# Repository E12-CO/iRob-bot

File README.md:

# iRob-bot

iRob-bot is a robot testing platform for Arduino and ROS2.
The goal is to have a autonomous robot with good odometry accuracy while having a simple motion control system that capable of manuvering complex movement.  

This robot is a part of R&D project at Robot club engineering KMITL (RB26).

# Why iRob-bot ?

Our club has a long experience with Mechanical and Electronics design. We have been doing these kind of works for almost three decades. But when it comes to autonomous robot. We're very new to this and still lacking a lot of fundamental skill such as motion control and planning. At the competition, our manual control robot worked very hard to gain a good amount of score, while our autonomous robot struggled to do a mission, let alone walking straight. 

Back in december 2023, there was a competition called ```CRU Robot Games```. 
This competition which each team has to compete using one manual control robot 
and one autonomous robot. In fact, we also participated in this same competition 
but without much success as we are very new to autonomous robot. (I personally participated back in 2022, That also my first time working with closed-loop 
control of DC motor with the autonomous robot, but again without much success).

There was a 3 wheeled omni robot from a team ```iRap```(robotics club from KMUTNB). I was intrigued by their autonomous robot, especially the motion control. Somehow it can do advanced motion like translational motion while also rotates 
around its own axis, or following the curve arc while also rotates around.

At the time I saw their robot in-action. I've had some previous experience from joining the club and working with holonomic robot (using mecanum/swiss wheel) . 
But nothing of us every came close to theirs. And we are still using ```robot oriented``` control. At best our robot did equiped with encoder and PI speed controlled for motor. But the robot still lack of a good motion
control system.

Tragidy strikes. Our club got critizied with a surprise budget cut by half. The reason was that we ```don't have a real work``` a.k.a we never win any of these competition despite a lots of work behind and knowledge that we gained and poured into each competition.

In out defense, we decided to start a R&D project to research and test out around the topic of robotics. The goal is to gain knowledge as much as possible to be used in competition. But also to prove them that every cent that we spend is turned into know-how that we then pass down to the next club member generation. 

This year is my last year at university as I will (hopefully) be graduated soon. I want to do something to help our junior members as a payback to what this club had taught me from the past 2 years. So I set out to learn and implement the motion control system. 

This is a good oppurtunity for me to revisit what I've seen back in 2023. I finally came up with a robot test platform called ```iRob-bot```, basically I "rob" the idea of using 3 wheeled omni robot from iRap, hence the name iRob-bot. along with the motion controller called ```Maneuv3r``` that will be on arduino and ROS2. 

# General Information

- Dimension : ⌀ : 145.4mm, Height included LiDAR : ~ 130mm
- Weight : ~0.4 kg
- Drivetrain ```omnidirectional 3 wheels (omni-wheel)```
- Motor ```N20 motor with 1:48 gearbox and 7PPR AB quadrature encoder```
- Drive ```DRV8835 on custom breakout board(sees Electronics folder)```
- Main controller ```ESP32 WROOM32```
- Odometry sensors
    - ```Wheel encoder``` (Moving average filtering)    
    - ```ADNS-5050``` optical flow sensor 
	- Wheel odometry and Optical Flow odometry fusion using ```complementary filter```
- IMU via I2C (9 axis GY-85 module)
    - ```ADXL345``` 3 axis Accelerometer (currently unused until I can implement EKF)
    - ```ITG3205``` 3 axis Gyro sensor
    - ```HMC5883L``` 3 axis Mag sensor (currently unused until I can implement EKF)
- LiDAR
    - ```HLS-LF2CD``` LiDAR (currently unused until I implemented ROS2 node)
- Digital Control running at ```125Hz```
    - PI speed control (No torque control)
    - PID position and orientation control
- ESP32 Dual core
    - Core 0 is working on Low-level control system
    - Core 1 is responsible for Networking task (BR/EDR or WiFi) and LiDAR reading (Work in progress)

# Folders
- Documents : Schematic and diagram PDFs and more soon.
- Electronics : Electronics design file (EAGLE cad and Fusion 360 format)
- Firmware : Arduino firmware
- Hardware : CAD design of the robot in Fusion 360 archive
- Software : ROS2 node (Coming soon)

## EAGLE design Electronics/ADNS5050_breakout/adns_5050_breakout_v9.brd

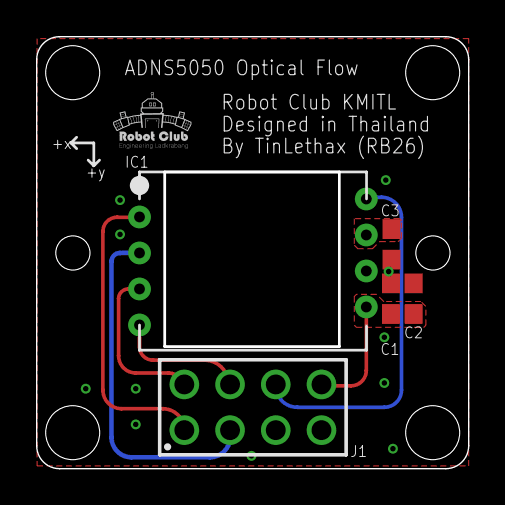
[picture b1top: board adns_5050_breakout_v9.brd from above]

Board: 2 copper layers, 23.9 x 23.9 mm, 5 parts (0 on the bottom side), 8 nets.

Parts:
C1, C3: 0.1uF; C0603
C2: 4.7uF; C0603
IC1: ADNS5050; WEIRD_DIP8
J1: 61300821121

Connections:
GND: C1.2, C2.2, C3.2, IC1.P$6, J1.5, J1.7
LED_OD: IC1.P$2, J1.3
NCS: IC1.P$4, J1.4
REGO: C3.1, IC1.P$7
RST: IC1.P$3, J1.2
SCLK: IC1.P$8, J1.6
SDIO: IC1.P$1, J1.1
VCC: C1.1, C2.1, IC1.P$5, J1.8

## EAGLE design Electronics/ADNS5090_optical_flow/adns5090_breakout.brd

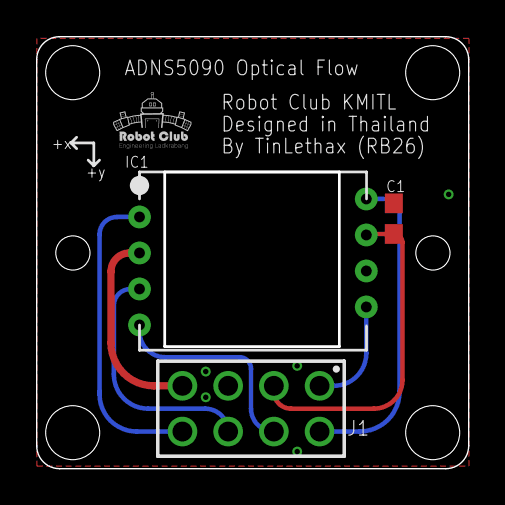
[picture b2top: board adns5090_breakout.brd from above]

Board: 2 copper layers, 23.9 x 23.9 mm, 3 parts (0 on the bottom side), 8 nets.

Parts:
C1: 0.1uF; C0603
IC1: ADNS5090; WEIRD_DIP8
J1: 61300821121

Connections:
3V3: C1.1, IC1.P$7, J1.3
/CS: IC1.P$4, J1.4
CLK: IC1.P$5, J1.1
GND: C1.2, IC1.P$6, J1.5
INT: IC1.P$3, J1.6
LED_K: IC1.P$2, J1.7
SI: IC1.P$8, J1.2
SO: IC1.P$1, J1.8

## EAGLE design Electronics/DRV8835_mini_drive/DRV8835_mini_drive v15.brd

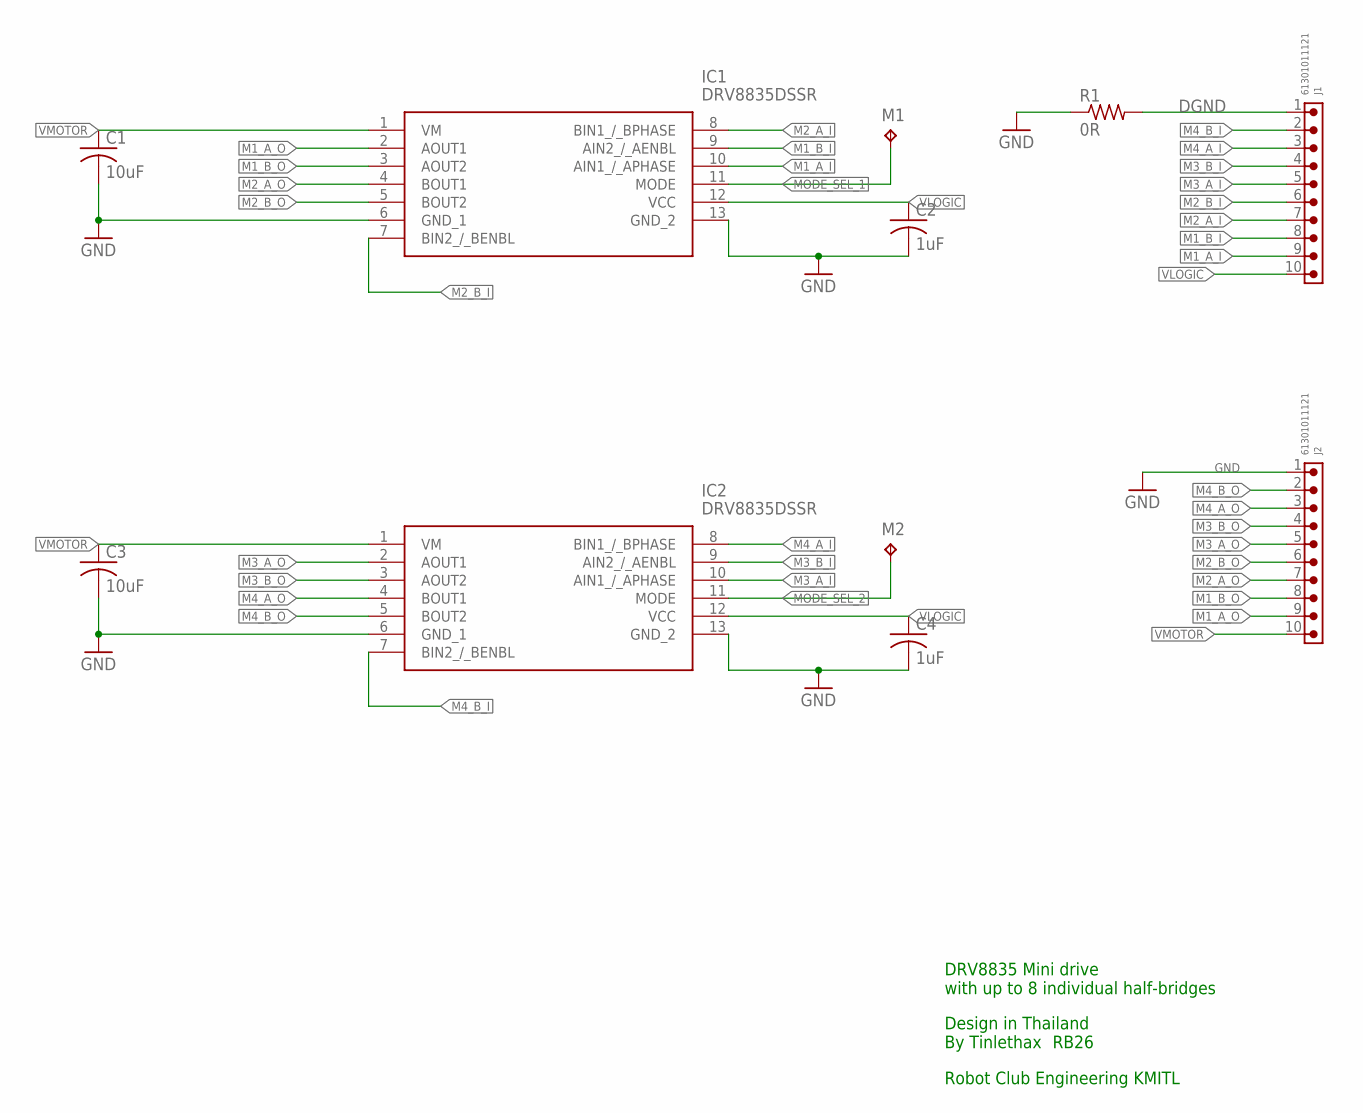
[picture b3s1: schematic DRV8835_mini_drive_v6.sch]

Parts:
C1, C3: 10uF; C0603
C2, C4: 1uF; C0603
IC1, IC2: DRV8835DSSR
J1, J2: 61301011121
M1, M2: TPTP10SQ; TP10SQ
R1: 0R; R0805

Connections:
DGND: J1.1, R1.2
GND: C1.2, C2.2, C3.2, C4.2, IC1.6 (GND_1), IC1.13 (GND_2), IC2.6 (GND_1), IC2.13 (GND_2), J2.1, R1.1
M1_A_I: IC1.10 (AIN1_/_APHASE), J1.9
M1_A_O: IC1.2 (AOUT1), J2.9
M1_B_I: IC1.9 (AIN2_/_AENBL), J1.8
M1_B_O: IC1.3 (AOUT2), J2.8
M2_A_I: IC1.8 (BIN1_/_BPHASE), J1.7
M2_A_O: IC1.4 (BOUT1), J2.7
M2_B_I: IC1.7 (BIN2_/_BENBL), J1.6
M2_B_O: IC1.5 (BOUT2), J2.6
M3_A_I: IC2.10 (AIN1_/_APHASE), J1.5
M3_A_O: IC2.2 (AOUT1), J2.5
M3_B_I: IC2.9 (AIN2_/_AENBL), J1.4
M3_B_O: IC2.3 (AOUT2), J2.4
M4_A_I: IC2.8 (BIN1_/_BPHASE), J1.3
M4_A_O: IC2.4 (BOUT1), J2.3
M4_B_I: IC2.7 (BIN2_/_BENBL), J1.2
M4_B_O: IC2.5 (BOUT2), J2.2
MODE_SEL_1: IC1.11 (MODE), M1.TP
MODE_SEL_2: IC2.11 (MODE), M2.TP
VLOGIC: C2.1, C4.1, IC1.12 (VCC), IC2.12 (VCC), J1.10
VMOTOR: C1.1, C3.1, IC1.1 (VM), IC2.1 (VM), J2.10

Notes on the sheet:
DRV8835 Mini drive with up to 8 individual half-bridges
Design in Thailand By Tinlethax
Robot Club Engineering KMITL
RB26

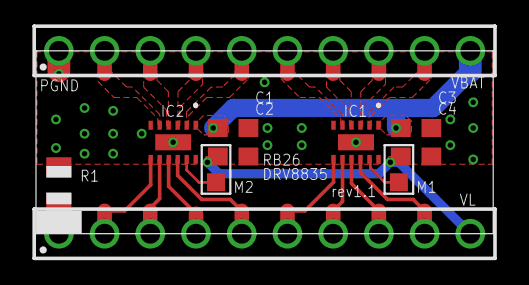
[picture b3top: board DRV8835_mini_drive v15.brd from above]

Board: 2 copper layers, 25.4 x 10.2 mm, 11 parts (0 on the bottom side), 22 nets.

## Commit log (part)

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2024-07-18 initial
2024-07-19 Updated the Gear ratio
2024-07-19 Corrected the Forward kinematic equation.
2024-07-19 Restore integrator (No value capping).
2024-07-19 Added separate Kp Ki and Kd for rotation in Twizzles.
2024-07-19 Gear ration is now 1:48, PID retuned.
2024-07-19 Store the offset in the integer format first, then convert it to float.
2024-07-20 SPI is now working properly. TODO: attach LED under the robot chassis.
2024-07-20 Fixed gyro calibration.
2024-07-20 Added description.
2024-07-20 Maneuv3r updates - Only pass the pointer of odometry and cmvvel just once at initialization. - Internal FSM only need 2 states. - Updated PID constant values - For now the ADNS5050 odometry will be o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
2024-07-22 Lots of updates : - Added odometry fusion between wheel odom and optical flow odom. Using simple complementary filter. EKF soon if I have more time. - Retuned PID, TODO : make twizzles rotate perfect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
2024-07-22 Corrected the Mouse control 2 register address typo and changed CPI to 1375.
2024-07-22 Correctly type cast int into float before calculating gyro offset value.
2024-07-23 Added motor drive electronics design.
2024-07-23 Added Robot mechanical design.
2024-07-25 no longer use error_percent.
2024-07-25 Change back distance tolerance back to 1cm. Twizzle rotate max at 2.5rad/s
2024-07-25 Added complementary filter between Gyro and Mag sensor. MORE TEST NEEDED.
2024-07-25 [W.I.P]Using packed struct for 8 bit access.
2024-07-25 removed unused variable.
2024-07-26 Retuned twizzles PID and added core 0 task preparing for networking taks.
2024-07-26 Read surface quality everytime we read the delta X and delta Y count. Useful for bad surface detection and lens cover warning.
2024-07-26 Lower the max angular velocity in twizzles and tighten up the rotation tolerance.
2024-07-26 Change motor 1 Kp to 4.0
2024-07-26 Added schematic of DRV8835 mini drive.
2024-07-26 Updated readme.
2024-07-26 Added block diagram of all control loops.
2024-07-30 minor changes to Block diagram drawing.
2024-07-30 Example code of using Bluepad32 with ESP32.
2024-07-30 Manual control code using Bluepad32 for demo show at K-eng 2024.
2024-07-30 Added rotate to north.
2024-08-01 absolute angular position CW rotate roll-over corrected.
2024-08-03 joytracker Ki retuned and moved to use typedef.
2024-09-15 - Fused Gyro with Magneto with conplementary. - now using position control instead of velocity command from joy.
2024-10-04 Added the breakout board design of ADNS5090, the better sensor compare to ADNS505.
2024-10-04 Maneuv3r (joycon version) is now in the format of .c/.h format. Will also do this in the autonomous code later.
2024-10-04 readjusted the conversion factor of the ADNS5050 after lens adjustment.
2024-11-25 Updated document with new docs.
2024-11-25 Added the F3 DISCO and ESP32 Upsized iROB hardware, also added original CAD design file.
2024-11-25 Added support code for iROB Upsized manual control (No Optical flow) TODO : Tidy the code.
2024-11-25 Now using macro to define the optical flow scaling constant.
2024-11-25 Removed unused part of the code.
2024-11-25 Added via stitching in the iRob Upsized ESP32DOIT design.
2024-12-19 Added firmware for iRob-upsized ESP32.
2025-01-02 Now making use of the DLPF of the MPU6050 and corrected the typo in calibratoin routine.
2025-01-29 Added firmware and electronics for iRob Upsized F3DISCO.
2025-02-25 Big update - maneuv3r is now default to absolute X,Y position instead of Dir,heading. - Retuned PID and FLO sensor scaling. - renamed stdodom to stdirob.

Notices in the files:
parts and their libraries:
Wurth_Connectors_WR-PHD: Copyright: Würth Elektronik
